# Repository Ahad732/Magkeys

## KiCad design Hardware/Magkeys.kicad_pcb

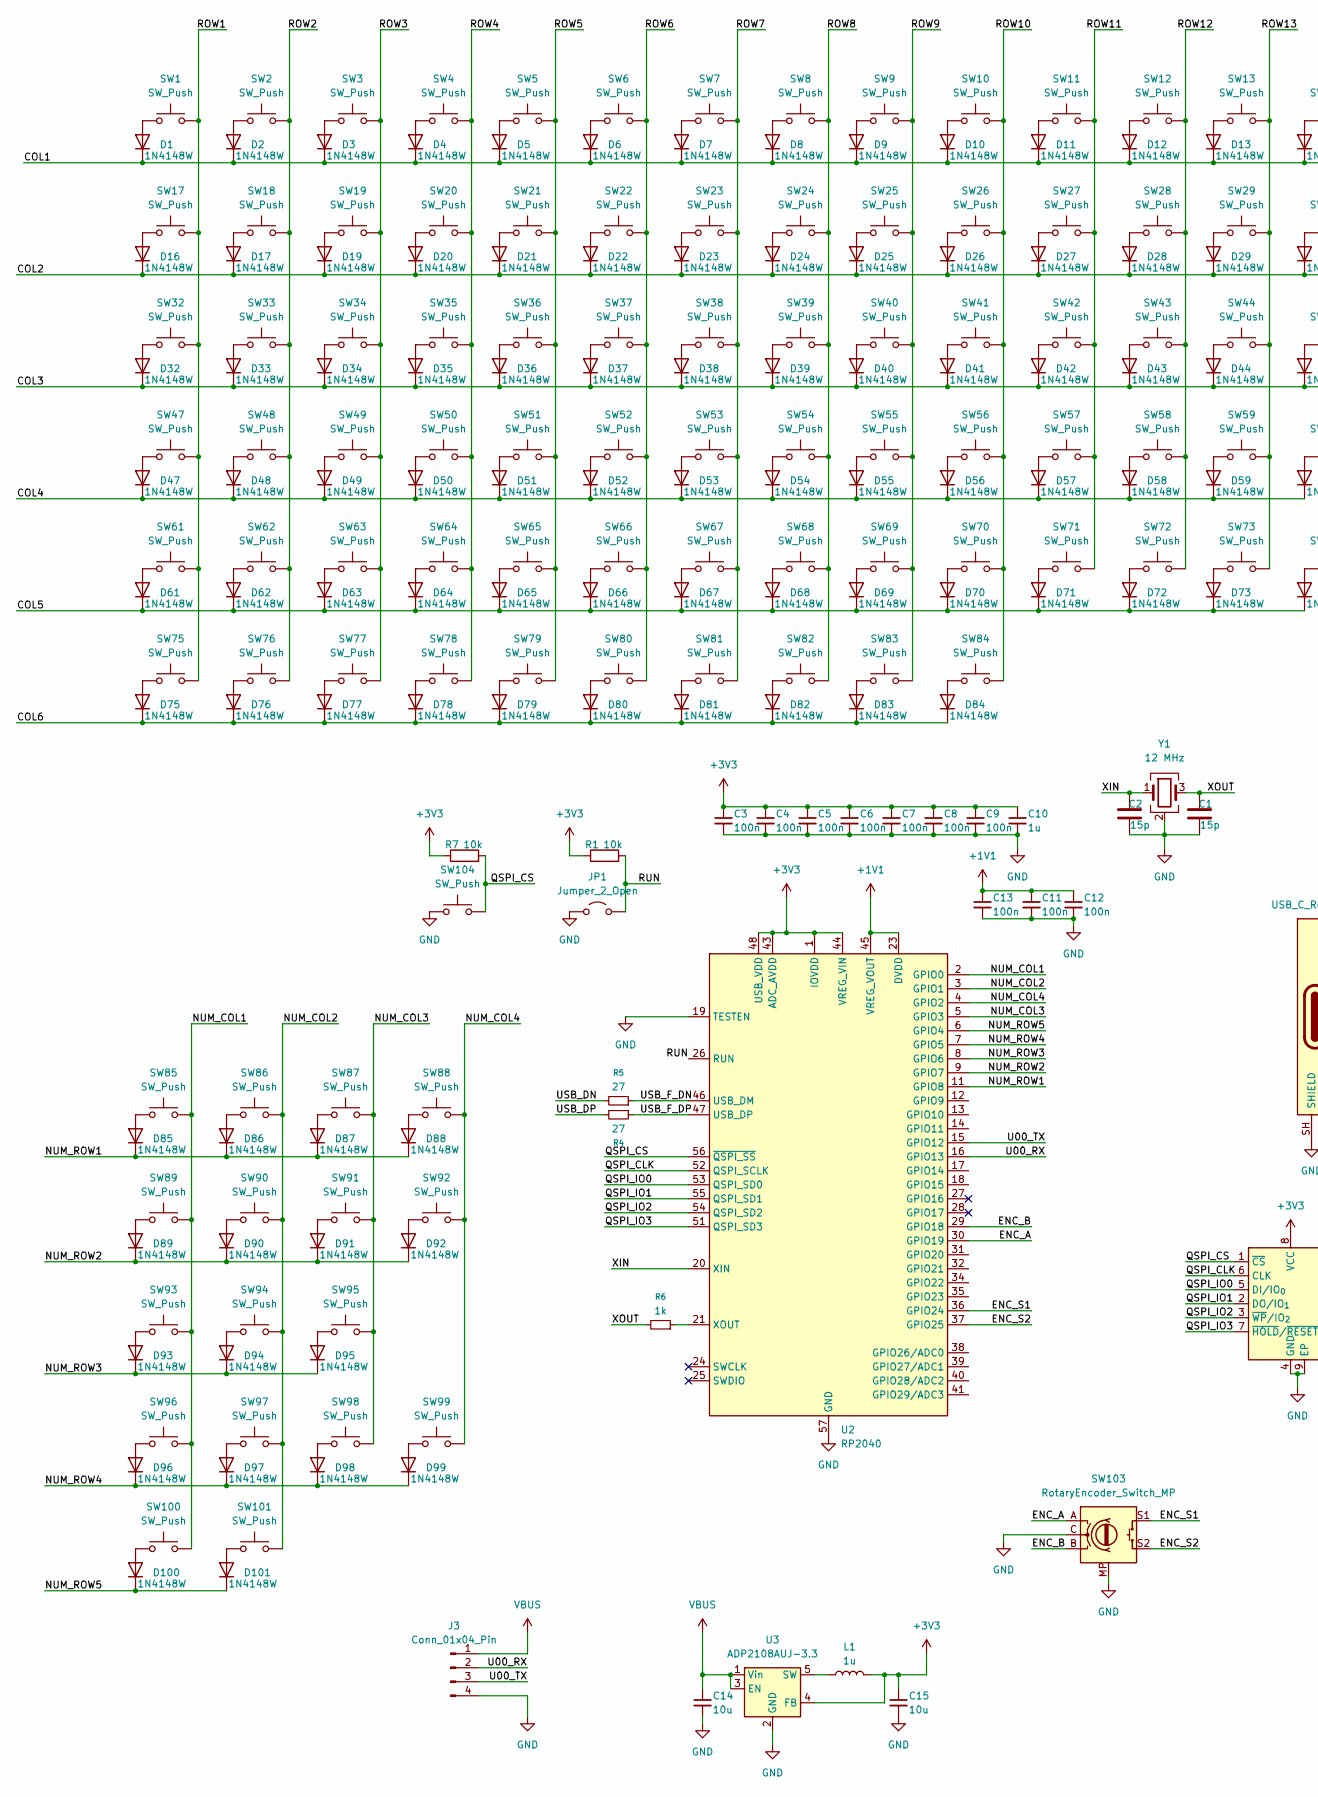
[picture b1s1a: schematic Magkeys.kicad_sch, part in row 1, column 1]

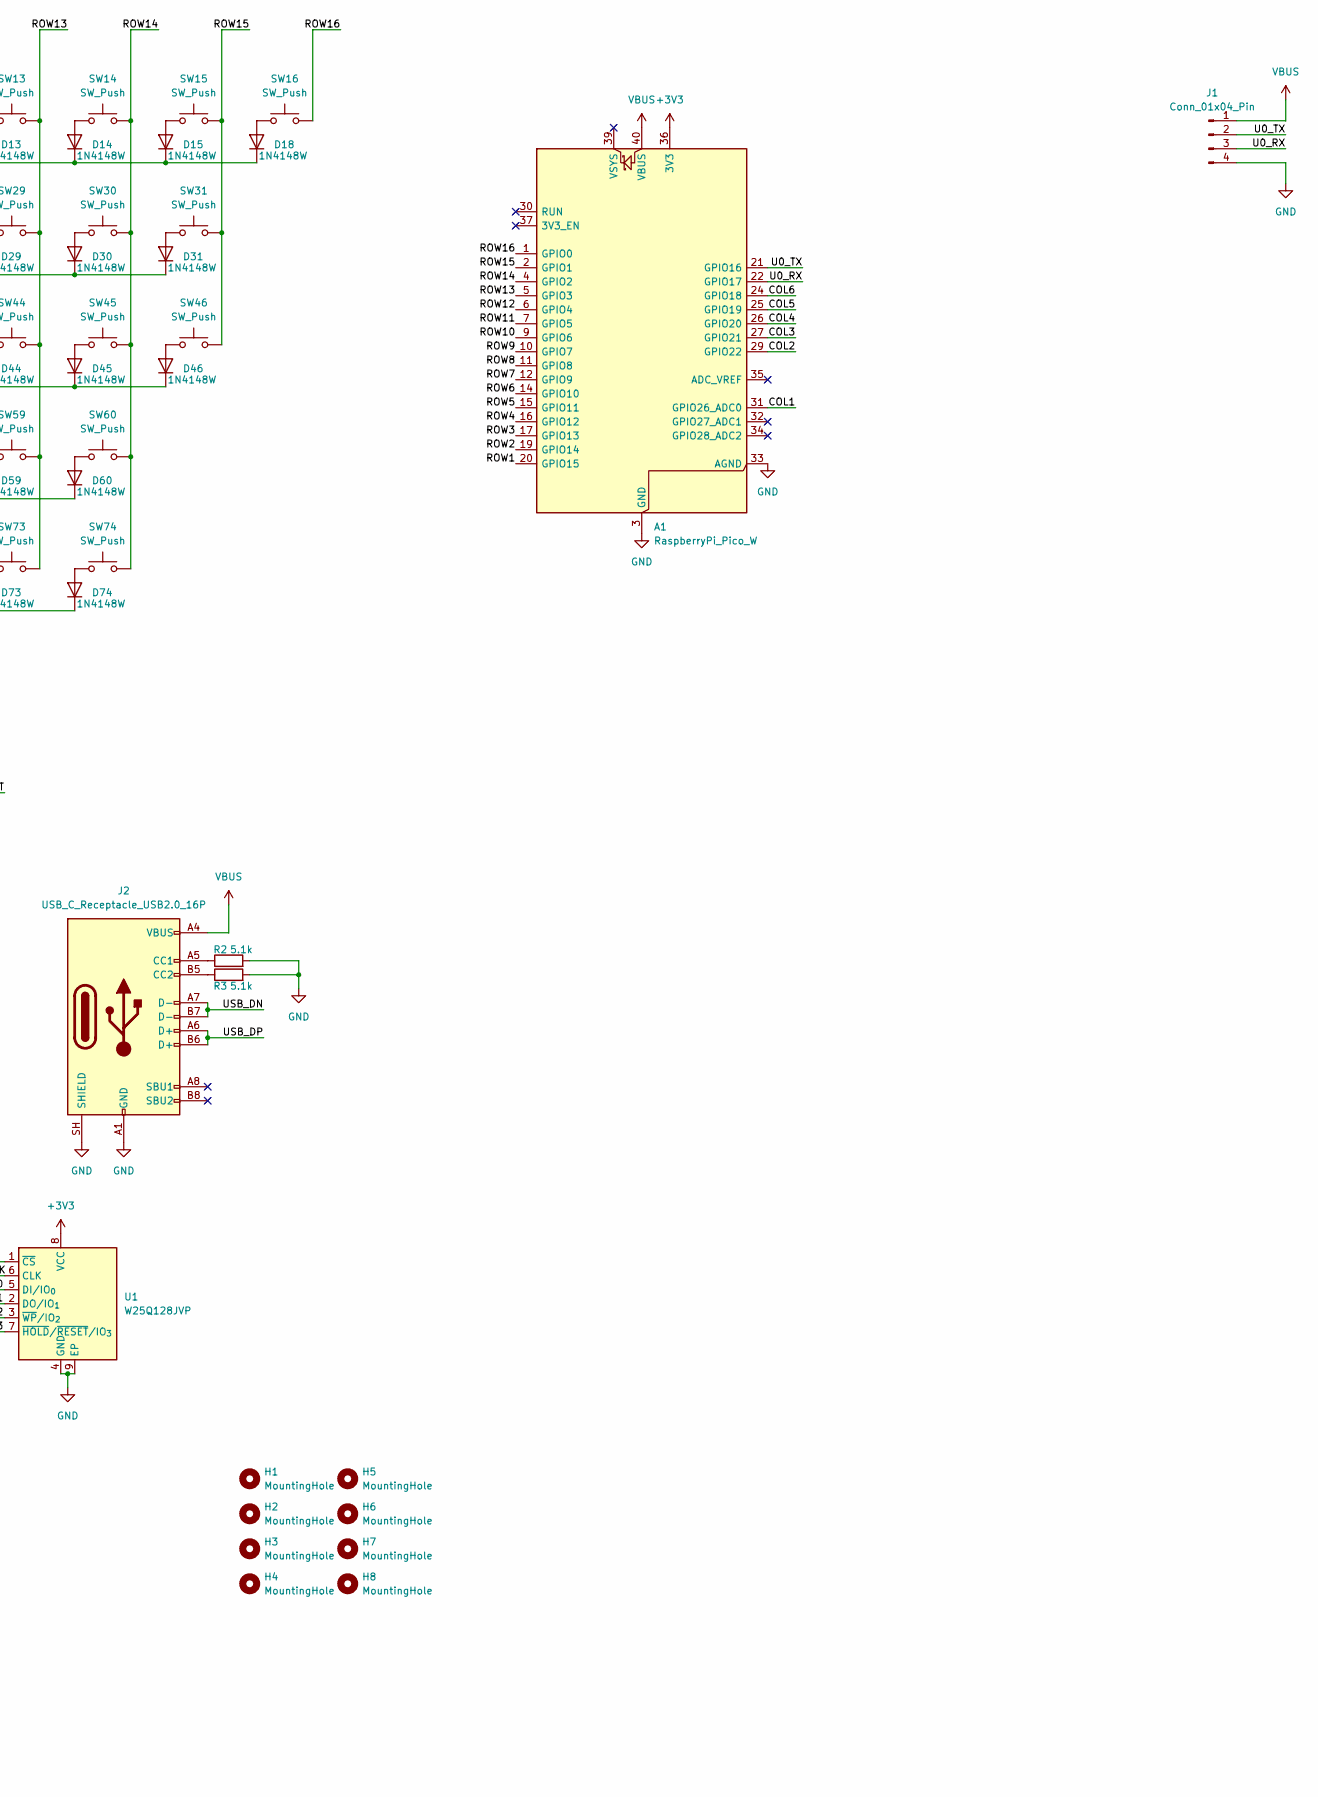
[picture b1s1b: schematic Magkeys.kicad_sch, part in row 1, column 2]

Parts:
A1: RaspberryPi_Pico_W; RaspberryPi_Pico_W_SMD
C1, C2: 15p; C_0402_1005Metric
C3, C4, C5, C6, C7, C8, C9, C11, C12, C13: 100n; C_0402_1005Metric
C10: 1u; C_0402_1005Metric
C14, C15: 10u; C_0402_1005Metric
D1, D2, D3, D4, D5, D6, D7, D8, D9, D10, D11, D12, D13, D14, D15, D16, D17, D18, D19, D20, D21, D22, D23, D24, D25, D26, D27, D28, D29, D30, D31, D32, D33, D34, D35, D36, D37, D38, D39, D40, D41, D42, D43, D44, D45, D46, D47, D48, D49, D50, D51, D52, D53, D54, D55, D56, D57, D58, D59, D60, D61, D62, D63, D64, D65, D66, D67, D68, D69, D70, D71, D72, D73, D74, D75, D76, D77, D78, D79, D80, D81, D82, D83, D84, D85, D86, D87, D88, D89, D90, D91, D92, D93, D94, D95, D96, D97, D98, D99, D100, D101: 1N4148W; D_SOD-123
H1, H2, H3, H4, H5, H6, H7, H8: MountingHole; MountingHole_3.2mm_M3
J1, J3: Conn_01x04_Pin; PinHeader_1x04_P2.54mm_Vertical
J2: USB_C_Receptacle_USB2.0_16P; USB_C_Receptacle_XKB_U262-16XN-4BVC11
JP1: Jumper_2_Open; SolderJumper-2_P1.3mm_Open_TrianglePad1.0x1.5mm
L1: 1u; L_0402_1005Metric
R1, R7: 10k; R_0402_1005Metric
R2, R3: 5.1k; R_0402_1005Metric
R4, R5: 27; R_0402_1005Metric
R6: 1k; R_0402_1005Metric
SW1, SW2, SW3, SW4, SW5, SW6, SW7, SW8, SW9, SW10, SW11, SW12, SW13, SW14, SW15, SW16, SW17, SW18, SW19, SW20, SW21, SW22, SW23, SW24, SW25, SW26, SW27, SW28, SW29, SW31, SW33, SW34, SW35, SW36, SW37, SW38, SW39, SW40, SW41, SW42, SW43, SW44, SW46, SW48, SW49, SW50, SW51, SW52, SW53, SW54, SW55, SW56, SW57, SW58, SW60, SW62, SW63, SW64, SW65, SW66, SW67, SW68, SW69, SW70, SW71, SW73, SW74, SW79, SW80, SW81, SW82, SW83, SW84, SW85, SW86, SW87, SW88, SW89, SW90, SW91, SW93, SW94, SW95, SW96, SW97, SW98, SW101: SW_Push; SW_Cherry_MX_1.00u_Plate
SW30, SW100: SW_Push; SW_Cherry_MX_2.00u_Plate
SW32, SW45: SW_Push; SW_Cherry_MX_1.50u_Plate
SW47, SW72: SW_Push; SW_Cherry_MX_1.75u_Plate
SW59, SW61: SW_Push; SW_Cherry_MX_2.25u_Plate
SW75, SW76, SW77: SW_Push; SW_Cherry_MX_1.25u_Plate
SW78: SW_Push; SW_Cherry_MX_6.25u_Plate
SW92, SW99: SW_Push; SW_Cherry_MX_2.00u_Vertical_Plate
SW103: RotaryEncoder_Switch_MP; RotaryEncoder_Alps_EC11E-Switch_Vertical_H20mm_MountingHoles
SW104: SW_Push; SW_SPST_PTS810
U1: W25Q128JVP; WSON-8-1EP_6x5mm_P1.27mm_EP3.4x4.3mm
U2: RP2040; QFN-56-1EP_7x7mm_P0.4mm_EP3.2x3.2mm
U3: ADP2108AUJ-3.3; TSOT-23-5
Y1: 12 MHz; Crystal_SMD_3225-4Pin_3.2x2.5mm

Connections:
+1V1: C11.1, C12.1, C13.1, U2.23 (DVDD), U2.45 (VREG_VOUT), U2.50 (DVDD)
+3V3: A1.36 (3V3), C3.1, C4.1, C5.1, C6.1, C7.1, C8.1, C9.1, C10.1, C15.1, L1.2, R1.1, R7.1, U1.8 (VCC), U2.1 (IOVDD), U2.10 (IOVDD), U2.22 (IOVDD), U2.33 (IOVDD), U2.42 (IOVDD), U2.43 (ADC_AVDD), U2.44 (VREG_VIN), U2.48 (USB_VDD), U2.49 (IOVDD), U3.4 (FB)
/COL1: A1.31 (GPIO26_ADC0), D1.1 (K), D2.1 (K), D3.1 (K), D4.1 (K), D5.1 (K), D6.1 (K), D7.1 (K), D8.1 (K), D9.1 (K), D10.1 (K), D11.1 (K), D12.1 (K), D13.1 (K), D14.1 (K), D15.1 (K), D18.1 (K)
/COL2: A1.29 (GPIO22), D16.1 (K), D17.1 (K), D19.1 (K), D20.1 (K), D21.1 (K), D22.1 (K), D23.1 (K), D24.1 (K), D25.1 (K), D26.1 (K), D27.1 (K), D28.1 (K), D29.1 (K), D30.1 (K), D31.1 (K)
/COL3: A1.27 (GPIO21), D32.1 (K), D33.1 (K), D34.1 (K), D35.1 (K), D36.1 (K), D37.1 (K), D38.1 (K), D39.1 (K), D40.1 (K), D41.1 (K), D42.1 (K), D43.1 (K), D44.1 (K), D45.1 (K), D46.1 (K)
/COL4: A1.26 (GPIO20), D47.1 (K), D48.1 (K), D49.1 (K), D50.1 (K), D51.1 (K), D52.1 (K), D53.1 (K), D54.1 (K), D55.1 (K), D56.1 (K), D57.1 (K), D58.1 (K), D59.1 (K), D60.1 (K)
/COL5: A1.25 (GPIO19), D61.1 (K), D62.1 (K), D63.1 (K), D64.1 (K), D65.1 (K), D66.1 (K), D67.1 (K), D68.1 (K), D69.1 (K), D70.1 (K), D71.1 (K), D72.1 (K), D73.1 (K), D74.1 (K)
/COL6: A1.24 (GPIO18), D75.1 (K), D76.1 (K), D77.1 (K), D78.1 (K), D79.1 (K), D80.1 (K), D81.1 (K), D82.1 (K), D83.1 (K), D84.1 (K)
/ENC_A: SW103.A, U2.30 (GPIO19)
/ENC_B: SW103.B, U2.29 (GPIO18)
/ENC_S1: SW103.S1, U2.36 (GPIO24)
/ENC_S2: SW103.S2, U2.37 (GPIO25)
/NUM_COL1: SW85.2, SW89.2, SW93.2, SW96.2, SW100.2, U2.2 (GPIO0)
/NUM_COL2: SW86.2, SW90.2, SW94.2, SW97.2, SW101.2, U2.3 (GPIO1)
/NUM_COL3: SW87.2, SW91.2, SW95.2, SW98.2, U2.5 (GPIO3)
/NUM_COL4: SW88.2, SW92.2, SW99.2, U2.4 (GPIO2)
/NUM_ROW1: D85.1 (K), D86.1 (K), D87.1 (K), D88.1 (K), U2.11 (GPIO8)
/NUM_ROW2: D89.1 (K), D90.1 (K), D91.1 (K), D92.1 (K), U2.9 (GPIO7)
/NUM_ROW3: D93.1 (K), D94.1 (K), D95.1 (K), U2.8 (GPIO6)
/NUM_ROW4: D96.1 (K), D97.1 (K), D98.1 (K), D99.1 (K), U2.7 (GPIO5)
/NUM_ROW5: D100.1 (K), D101.1 (K), U2.6 (GPIO4)
/QSPI_CLK: U1.6 (CLK), U2.52 (QSPI_SCLK)
/QSPI_CS: R7.2, SW104.2, U1.1 (~CS), U2.56 (~QSPI_SS)
/QSPI_IO0: U1.5 (DI/IO_{0}), U2.53 (QSPI_SD0)
/QSPI_IO1: U1.2 (DO/IO_{1}), U2.55 (QSPI_SD1)
/QSPI_IO2: U1.3 (~WP/IO_{2}), U2.54 (QSPI_SD2)
/QSPI_IO3: U1.7 (~HOLD/~RESET/IO_{3}), U2.51 (QSPI_SD3)
/ROW1: A1.20 (GPIO15), SW1.2, SW17.2, SW32.2, SW47.2, SW61.2, SW75.2
/ROW2: A1.19 (GPIO14), SW2.2, SW18.2, SW33.2, SW48.2, SW62.2, SW76.2
/ROW3: A1.17 (GPIO13), SW3.2, SW19.2, SW34.2, SW49.2, SW63.2, SW77.2
/ROW4: A1.16 (GPIO12), SW4.2, SW20.2, SW35.2, SW50.2, SW64.2, SW78.2
/ROW5: A1.15 (GPIO11), SW5.2, SW21.2, SW36.2, SW51.2, SW65.2, SW79.2
/ROW6: A1.14 (GPIO10), SW6.2, SW22.2, SW37.2, SW52.2, SW66.2, SW80.2
/ROW7: A1.12 (GPIO9), SW7.2, SW23.2, SW38.2, SW53.2, SW67.2, SW81.2
/ROW8: A1.11 (GPIO8), SW8.2, SW24.2, SW39.2, SW54.2, SW68.2, SW82.2
/ROW9: A1.10 (GPIO7), SW9.2, SW25.2, SW40.2, SW55.2, SW69.2, SW83.2
/ROW10: A1.9 (GPIO6), SW10.2, SW26.2, SW41.2, SW56.2, SW70.2, SW84.2
/ROW11: A1.7 (GPIO5), SW11.2, SW27.2, SW42.2, SW57.2, SW71.2
/ROW12: A1.6 (GPIO4), SW12.2, SW28.2, SW43.2, SW58.2, SW72.2
/ROW13: A1.5 (GPIO3), SW13.2, SW29.2, SW44.2, SW59.2, SW73.2
/ROW14: A1.4 (GPIO2), SW14.2, SW30.2, SW45.2, SW60.2, SW74.2
/ROW15: A1.2 (GPIO1), SW15.2, SW31.2, SW46.2
/ROW16: A1.1 (GPIO0), SW16.2
/RUN: JP1.2 (B), R1.2, U2.26 (RUN)
/U00_RX: J3.2, U2.16 (GPIO13)
/U0_RX: A1.22 (GPIO17), J1.3
/U00_TX: J3.3, U2.15 (GPIO12)
/U0_TX: A1.21 (GPIO16), J1.2
/USB_DN: J2.A7 (D-), J2.B7 (D-), R5.2
/USB_DP: J2.A6 (D+), J2.B6 (D+), R4.2
/USB_F_DN: R5.1, U2.46 (USB_DM)
/USB_F_DP: R4.1, U2.47 (USB_DP)
/XIN: C2.1, U2.20 (XIN), Y1.1
/XOUT: C1.1, R6.2, Y1.3
GND: A1.3 (GND), A1.8 (GND), A1.13 (GND), A1.18 (GND), A1.23 (GND), A1.28 (GND), A1.33 (AGND), A1.38 (GND), C1.2, C2.2, C3.2, C4.2, C5.2, C6.2, C7.2, C8.2, C9.2, C10.2, C11.2, C12.2, C13.2, C14.2, C15.2, J1.4, J2.A1 (GND), J2.A12 (GND), J2.B1 (GND), J2.B12 (GND), J2.SH (SHIELD), J3.4, JP1.1 (A), R2.2, R3.2, SW103.C, SW103.MP, SW104.1, U1.4 (GND), U1.9 (EP), U2.19 (TESTEN), U2.57 (GND), U3.2 (GND), Y1.2 (G), Y1.4 (G)
unnamed: D1.2 (A), SW1.1
unnamed: D2.2 (A), SW2.1
unnamed: D3.2 (A), SW3.1
unnamed: D4.2 (A), SW4.1
unnamed: D5.2 (A), SW5.1
unnamed: D6.2 (A), SW6.1
unnamed: D7.2 (A), SW7.1
unnamed: D8.2 (A), SW8.1
unnamed: D9.2 (A), SW9.1
unnamed: D10.2 (A), SW10.1
unnamed: D11.2 (A), SW11.1
unnamed: D12.2 (A), SW12.1
unnamed: D13.2 (A), SW13.1
unnamed: D14.2 (A), SW14.1
unnamed: D15.2 (A), SW15.1
unnamed: D16.2 (A), SW17.1
unnamed: D17.2 (A), SW18.1
unnamed: D18.2 (A), SW16.1
unnamed: D19.2 (A), SW19.1
unnamed: D20.2 (A), SW20.1
unnamed: D21.2 (A), SW21.1
unnamed: D22.2 (A), SW22.1
unnamed: D23.2 (A), SW23.1
unnamed: D24.2 (A), SW24.1
unnamed: D25.2 (A), SW25.1
unnamed: D26.2 (A), SW26.1
unnamed: D27.2 (A), SW27.1
unnamed: D28.2 (A), SW28.1
unnamed: D29.2 (A), SW29.1
unnamed: D30.2 (A), SW30.1
unnamed: D31.2 (A), SW31.1
unnamed: D32.2 (A), SW32.1
unnamed: D33.2 (A), SW33.1
unnamed: D34.2 (A), SW34.1
unnamed: D35.2 (A), SW35.1
unnamed: D36.2 (A), SW36.1
unnamed: D37.2 (A), SW37.1
unnamed: D38.2 (A), SW38.1
unnamed: D39.2 (A), SW39.1
unnamed: D40.2 (A), SW40.1
unnamed: D41.2 (A), SW41.1
unnamed: D42.2 (A), SW42.1
unnamed: D43.2 (A), SW43.1
unnamed: D44.2 (A), SW44.1
unnamed: D45.2 (A), SW45.1
unnamed: D46.2 (A), SW46.1
unnamed: D47.2 (A), SW47.1
unnamed: D48.2 (A), SW48.1
unnamed: D49.2 (A), SW49.1
unnamed: D50.2 (A), SW50.1
unnamed: D51.2 (A), SW51.1
unnamed: D52.2 (A), SW52.1
unnamed: D53.2 (A), SW53.1
unnamed: D54.2 (A), SW54.1
unnamed: D55.2 (A), SW55.1
unnamed: D56.2 (A), SW56.1
unnamed: D57.2 (A), SW57.1
unnamed: D58.2 (A), SW58.1
unnamed: D59.2 (A), SW59.1
unnamed: D60.2 (A), SW60.1
unnamed: D61.2 (A), SW61.1
unnamed: D62.2 (A), SW62.1
unnamed: D63.2 (A), SW63.1
unnamed: D64.2 (A), SW64.1
unnamed: D65.2 (A), SW65.1
unnamed: D66.2 (A), SW66.1
unnamed: D67.2 (A), SW67.1
unnamed: D68.2 (A), SW68.1
unnamed: D69.2 (A), SW69.1
unnamed: D70.2 (A), SW70.1
unnamed: D71.2 (A), SW71.1
unnamed: D72.2 (A), SW72.1
unnamed: D73.2 (A), SW73.1
unnamed: D74.2 (A), SW74.1
unnamed: D75.2 (A), SW75.1
unnamed: D76.2 (A), SW76.1
unnamed: D77.2 (A), SW77.1
unnamed: D78.2 (A), SW78.1
unnamed: D79.2 (A), SW79.1
unnamed: D80.2 (A), SW80.1
unnamed: D81.2 (A), SW81.1
unnamed: D82.2 (A), SW82.1
unnamed: D83.2 (A), SW83.1
unnamed: D84.2 (A), SW84.1
unnamed: D85.2 (A), SW85.1
unnamed: D86.2 (A), SW86.1
unnamed: D87.2 (A), SW87.1
unnamed: D88.2 (A), SW88.1
unnamed: D89.2 (A), SW89.1
unnamed: D90.2 (A), SW90.1
unnamed: D91.2 (A), SW91.1
unnamed: D92.2 (A), SW92.1
unnamed: D93.2 (A), SW93.1
unnamed: D94.2 (A), SW94.1
unnamed: D95.2 (A), SW95.1
unnamed: D96.2 (A), SW96.1
unnamed: D97.2 (A), SW97.1
unnamed: D98.2 (A), SW98.1
unnamed: D99.2 (A), SW99.1
unnamed: D100.2 (A), SW100.1
unnamed: D101.2 (A), SW101.1
unnamed: J2.A5 (CC1), R2.1
unnamed: J2.B5 (CC2), R3.1
unnamed: R6.1, U2.21 (XOUT)
unnamed: L1.1, U3.5 (SW)
VBUS: A1.40 (VBUS), C14.1, J1.1, J2.A4 (VBUS), J2.A9 (VBUS), J2.B4 (VBUS), J2.B9 (VBUS), J3.1, U3.1 (Vin), U3.3 (EN)

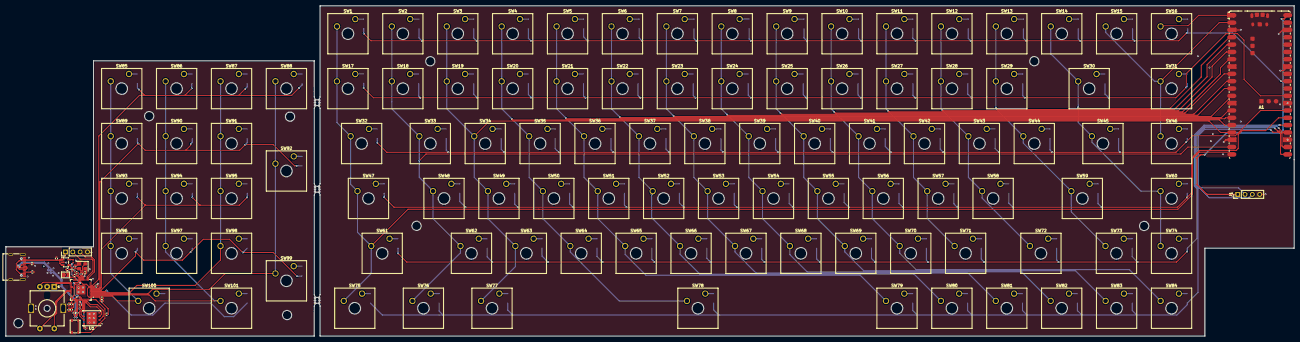
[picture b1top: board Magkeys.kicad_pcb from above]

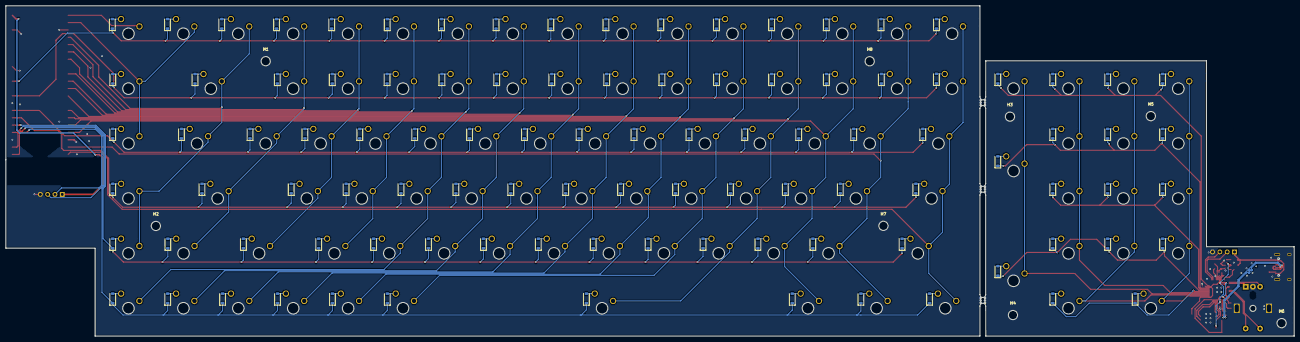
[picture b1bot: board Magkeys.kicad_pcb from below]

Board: 2 copper layers, 447.0 x 114.6 mm, 244 parts (109 on the bottom side), 161 nets.

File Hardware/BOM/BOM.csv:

Designator,Footprint,Value,Quantity,Price,Link
A1,RaspberryPi_Pico_W_SMD,RaspberryPi_Pico_W,1,6.71,https://robu.in/product/raspberry-pi-pico-w/
"C1, C2",402,15p,50,0.08,https://www.lcsc.com/product-detail/C696887.html
"C10, L1",402,1u,50,0.22,https://www.lcsc.com/product-detail/C2887021.html
"C11, C12, C13, C3, C4, C5, C6, C7, C8, C9",402,100n,100,0.14,https://www.lcsc.com/product-detail/C285038.html
"C14, C15",402,10u,20,0.44,https://www.lcsc.com/product-detail/C23692971.html
D1-D102,D_SOD-123,1N4148W,150,1.26,https://www.lcsc.com/product-detail/C917030.html
"J1, J3",PinHeader_1x04_P2.54mm_Vertical,Conn_01x04_Pin (pogo connector),2 pairs,3.7,https://probots.co.in/4p-magnetic-spring-loaded-pogo-pin-mal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
J2,USB_C_Receptacle_XKB_U262-16XN-4BVC11,USB_C_Receptacle_USB2.0_16P,10,0.53,https://www.lcsc.com/product-detail/C42400252.html
"R1, R7",402,10k,100,0.07,https://www.lcsc.com/product-detail/C54920614.html
"R2, R3",402,5.1k,100,0.06,https://www.lcsc.com/product-detail/C54920813.html
"R4, R5",402,27,100,0.06,https://www.lcsc.com/product-detail/C54920766.html
R6,402,1k,100,0.07,https://www.lcsc.com/product-detail/C54920633.html
SW1-SW102,SW_Cherry_MX_1.00u_Plate,SW_Push,1 pack of 110,15.5,https://stackskb.com/store/click-inc-hp-switch-pack-of-110/
SW103,RotaryEncoder_Alps_EC11E-Switch_Vertical_H20mm_MountingHoles,RotaryEncoder_Switch_MP,2,4.63,https://www.lcsc.com/product-detail/C470753.html
SW104,SW_SPST_PTS810,SW_Push,5,1.71,https://www.lcsc.com/product-detail/C221895.html
U1,WSON-8-1EP_6x5mm_P1.27mm_EP3.4x4.3mm,W25Q128JVP,2,6.83,https://www.lcsc.com/product-detail/C190862.html
U2,QFN-56-1EP_7x7mm_P0.4mm_EP3.2x3.2mm,RP2040,2,2,https://www.lcsc.com/product-detail/C2040.html
U3,TSOT-23-5,ADP2108AUJ-3.3,2,9.69,https://www.lcsc.com/product-detail/C143875.html
Y1,Crystal_SMD_3225-4Pin_3.2x2.5mm,12 MHz,10,0.55,https://www.lcsc.com/product-detail/C16197268.html
,,Keycaps,1,10.32,https://www.amazon.in/ZORBES%C2%AE-Forged-Texture-Mechanical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
,,,Parts shipping,7.04,
,,,PCB+Shipping,28.7,
,,,Total,100.31,
